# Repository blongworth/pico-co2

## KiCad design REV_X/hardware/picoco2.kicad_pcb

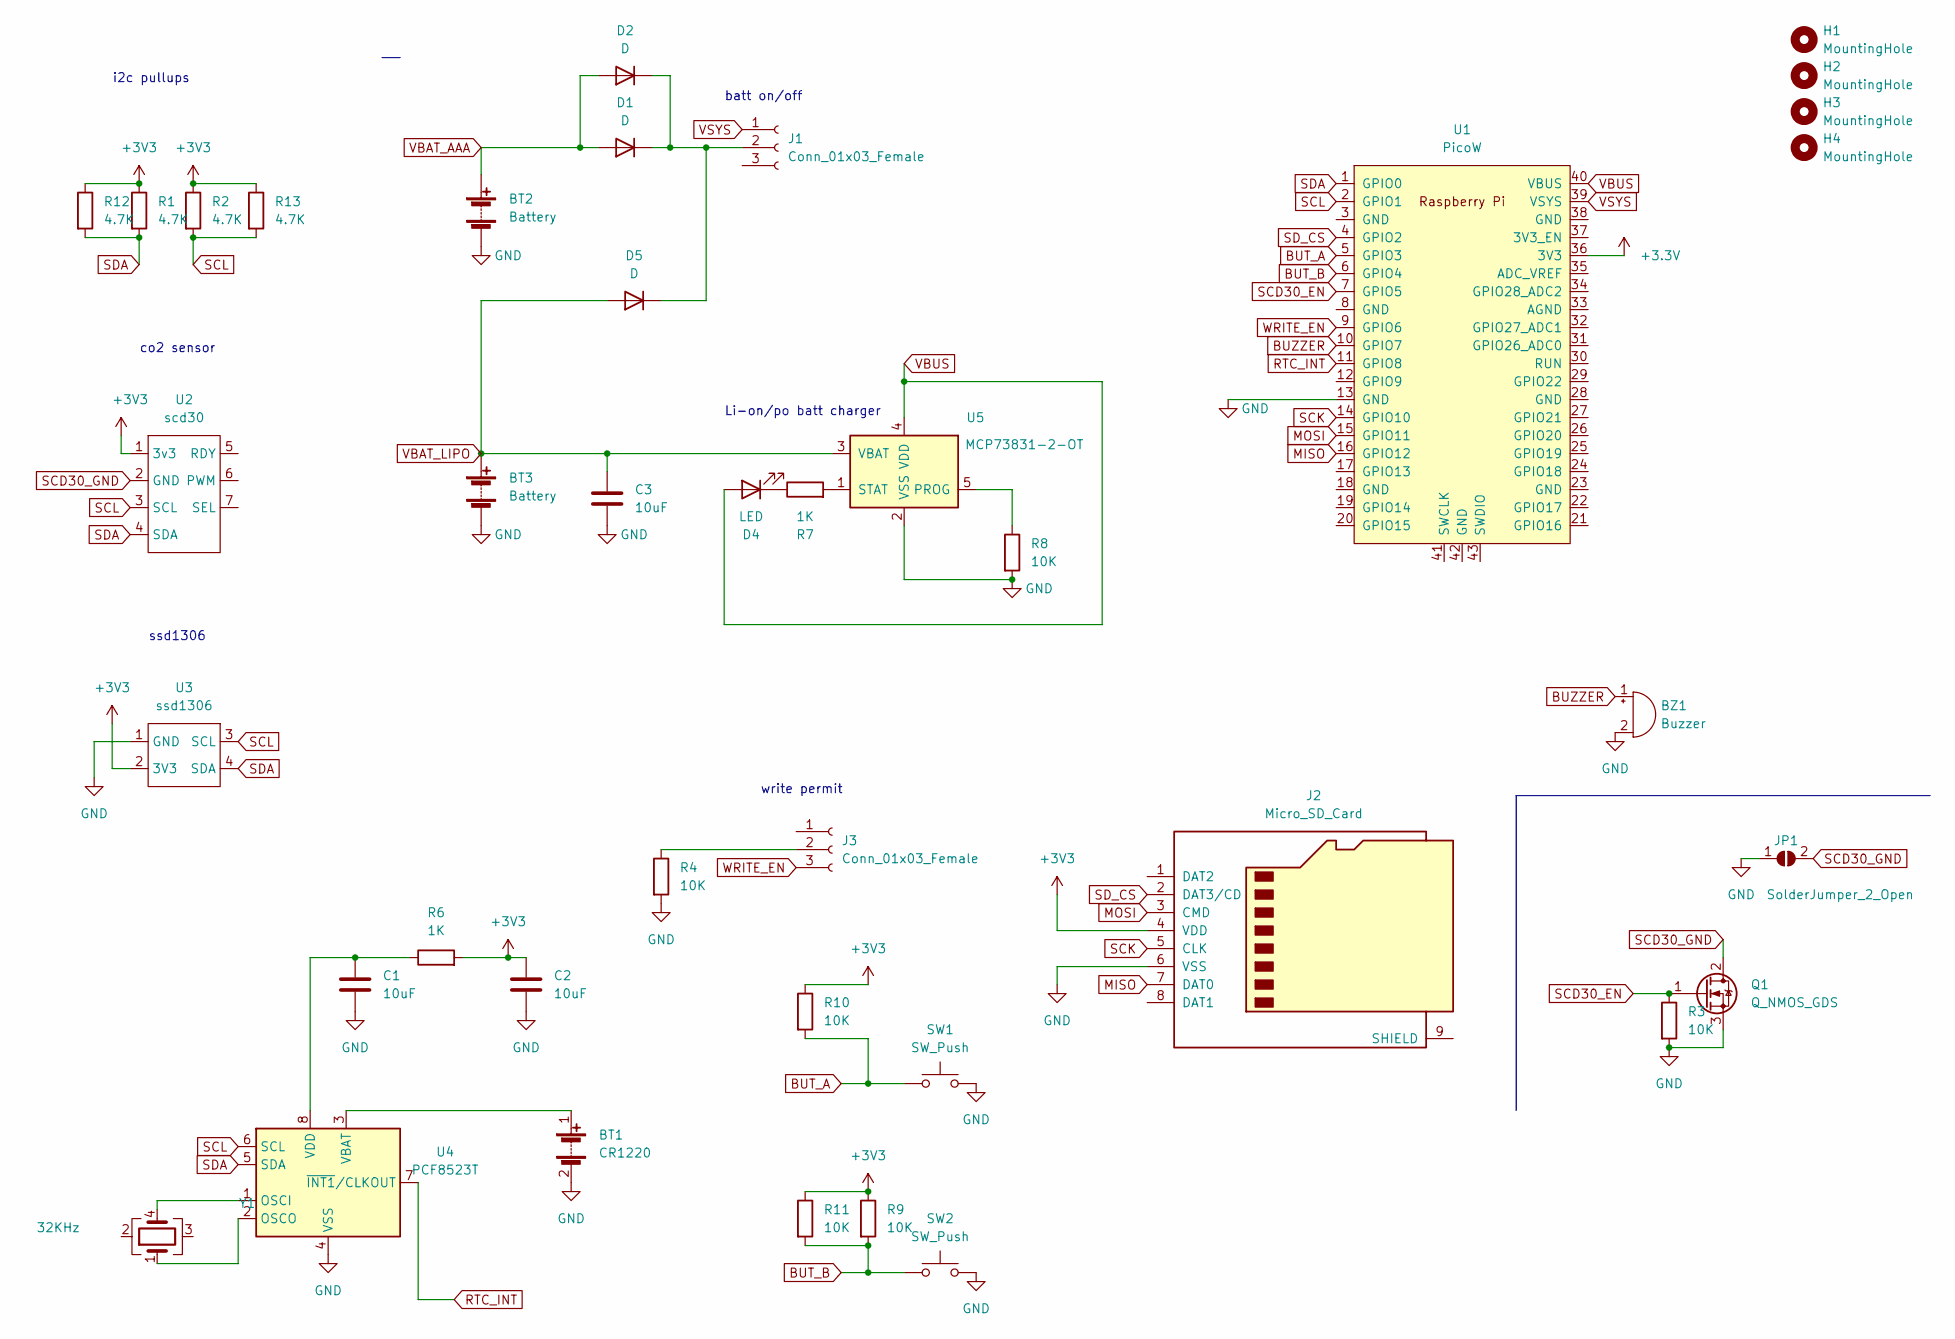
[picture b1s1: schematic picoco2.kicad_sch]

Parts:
BT1: CR1220; CR1220-2
BT2: Battery; BatteryHolder_Keystone_2468_2xAAA
BT3: Battery; JST_PH_S2B-PH-SM4-TB_1x02-1MP_P2.00mm_Horizontal
BZ1: Buzzer; MagneticBuzzer_Kobitone_254-EMB84Q-RO
C1, C2, C3: 10uF; C_0603_1608Metric_Pad1.08x0.95mm_HandSolder
D1, D5: D; D_SOD-123F
D2: D; D_5W_P10.16mm_Horizontal
D4: LED; LED_0603_1608Metric_Pad1.05x0.95mm_HandSolder
H1, H2, H3, H4: MountingHole; MountingHole_3.2mm_M3
J1, J3: Conn_01x03_Female; PinSocket_1x03_P2.54mm_Vertical
J2: Micro_SD_Card; DM3D-SF_outline
JP1: SolderJumper_2_Open; SolderJumper-2_P1.3mm_Open_Pad1.0x1.5mm
Q1: Q_NMOS_GDS; SOT-23
R1, R2: 4.7K; R_0603_1608Metric_Pad0.98x0.95mm_HandSolder
R3, R4, R8, R9: 10K; R_0603_1608Metric_Pad0.98x0.95mm_HandSolder
R6, R7: 1K; R_0603_1608Metric_Pad0.98x0.95mm_HandSolder
R10, R11: 10K; R_Axial_DIN0204_L3.6mm_D1.6mm_P7.62mm_Horizontal
R12, R13: 4.7K; R_Axial_DIN0204_L3.6mm_D1.6mm_P7.62mm_Horizontal
SW1, SW2: SW_Push; SW_Tactile_SPST_Angled_PTS645Vx31-2LFS
U1: PicoW; RPi_PicoW_SMD
U2: scd30; scd30_a
U3: ssd1306; ssd1306_a
U4: PCF8523T; SOIC-8_3.9x4.9mm_P1.27mm
U5: MCP73831-2-OT; SOT-23-5
Y1: 32KHz; Crystal_SMD_Abracon_ABS25-4Pin_8.0x3.8mm

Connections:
BUT_A: R10.2, SW1.1, U1.5 (GPIO3)
BUT_B: R9.2, R11.2, SW2.1, U1.6 (GPIO4)
BUZZER: BZ1.1 (-), U1.10 (GPIO7)
GND: BT1.2 (-), BT2.2 (-), BT3.2 (-), BZ1.2 (+), C1.2, C2.2, C3.2, J2.6 (VSS), JP1.1 (A), Q1.3 (S), R3.2, R4.2, R8.2, SW1.2, SW2.2, U1.13 (GND), U3.1 (GND), U4.4 (VSS), U5.2 (VSS)
MISO: J2.7 (DAT0), U1.16 (GPIO12)
MOSI: J2.3 (CMD), U1.15 (GPIO11)
unnamed: BT1.1 (+), U4.3 (VBAT)
unnamed: C1.1, R6.1, U4.8 (VDD)
unnamed: D1.1 (K), D2.1 (K), D5.1 (K), J1.2
unnamed: D4.1 (K), R7.1
unnamed: J3.2, R4.1
unnamed: R7.2, U5.1 (STAT)
unnamed: R8.1, U5.5 (PROG)
unnamed: U4.1 (OSCI), Y1.4
unnamed: U4.2 (OSCO), Y1.1
RTC_INT: U1.11 (GPIO8), U4.7 (~INT1/CLKOUT)
SCD30_EN: Q1.1 (G), R3.1, U1.7 (GPIO5)
SCD30_GND: JP1.2 (B), Q1.2 (D), U2.2 (GND)
SCK: J2.5 (CLK), U1.14 (GPIO10)
SCL: R2.2, R13.2, U1.2 (GPIO1), U2.3 (SCL), U3.3 (SCL), U4.6 (SCL)
SDA: R1.2, R12.2, U1.1 (GPIO0), U2.4 (SDA), U3.4 (SDA), U4.5 (SDA)
SD_CS: J2.2 (DAT3/CD), U1.4 (GPIO2)
VBAT_AAA: BT2.1 (+), D1.2 (A), D2.2 (A)
VBAT_LIPO: BT3.1 (+), C3.1, D5.2 (A), U5.3 (VBAT)
VBUS: D4.2 (A), U1.40 (VBUS), U5.4 (VDD)
VSYS: J1.1, U1.39 (VSYS)
WRITE_EN: J3.3, U1.9 (GPIO6)

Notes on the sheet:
i2c pullups
write permit
batt on/off
Li-on/po batt charger
co2 sensor
ssd1306

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
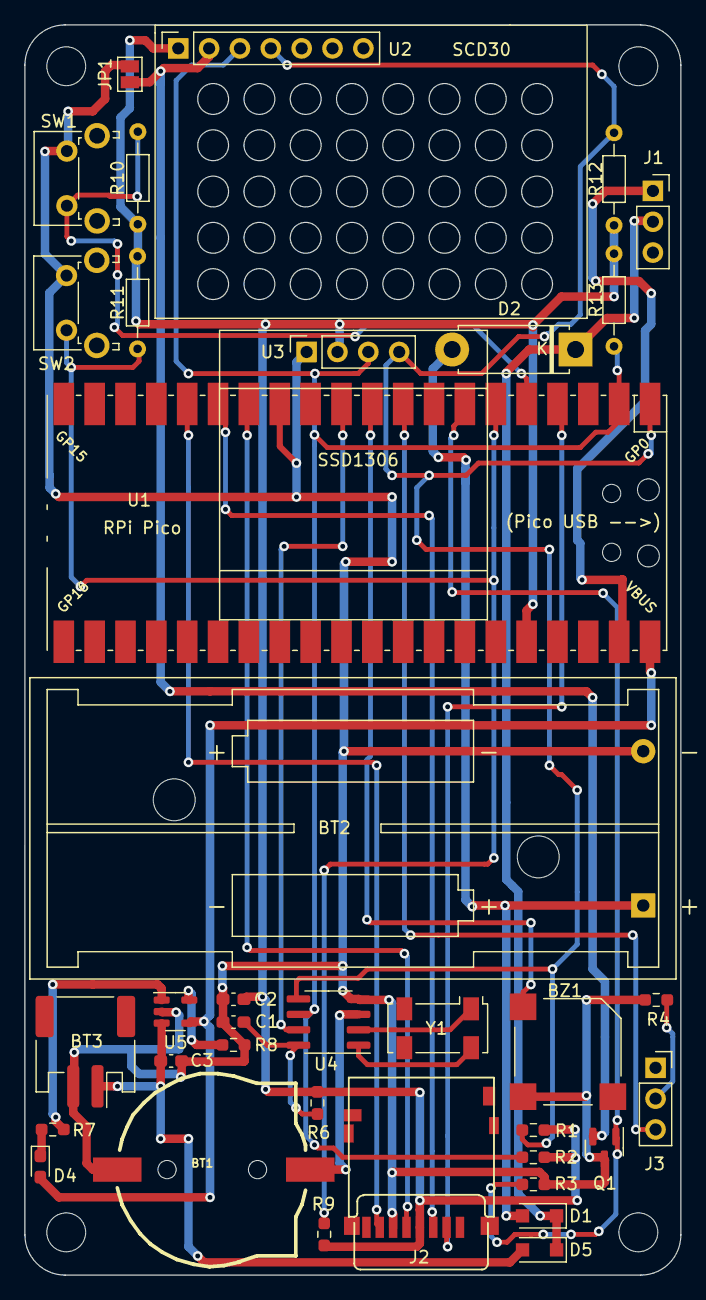
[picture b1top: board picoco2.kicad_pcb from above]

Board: 2 copper layers, 54.0 x 102.9 mm, 40 parts (0 on the bottom side), 28 nets.

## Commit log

2023-03-04 add pico 3V3 and GND
2023-03-05 Attempting to handle AIO MemoryError
